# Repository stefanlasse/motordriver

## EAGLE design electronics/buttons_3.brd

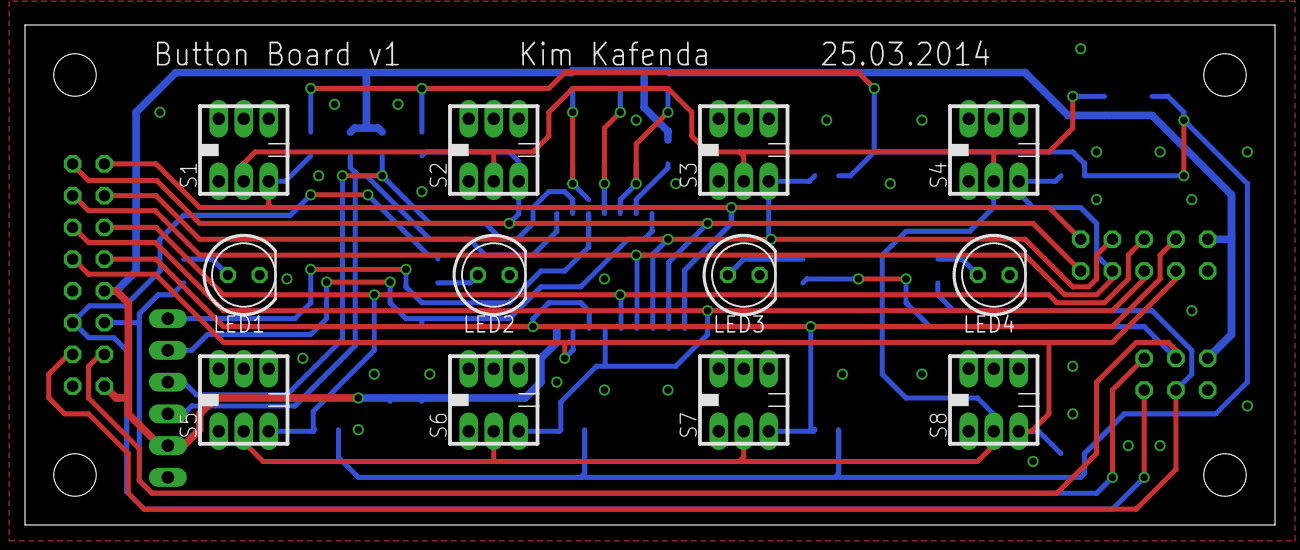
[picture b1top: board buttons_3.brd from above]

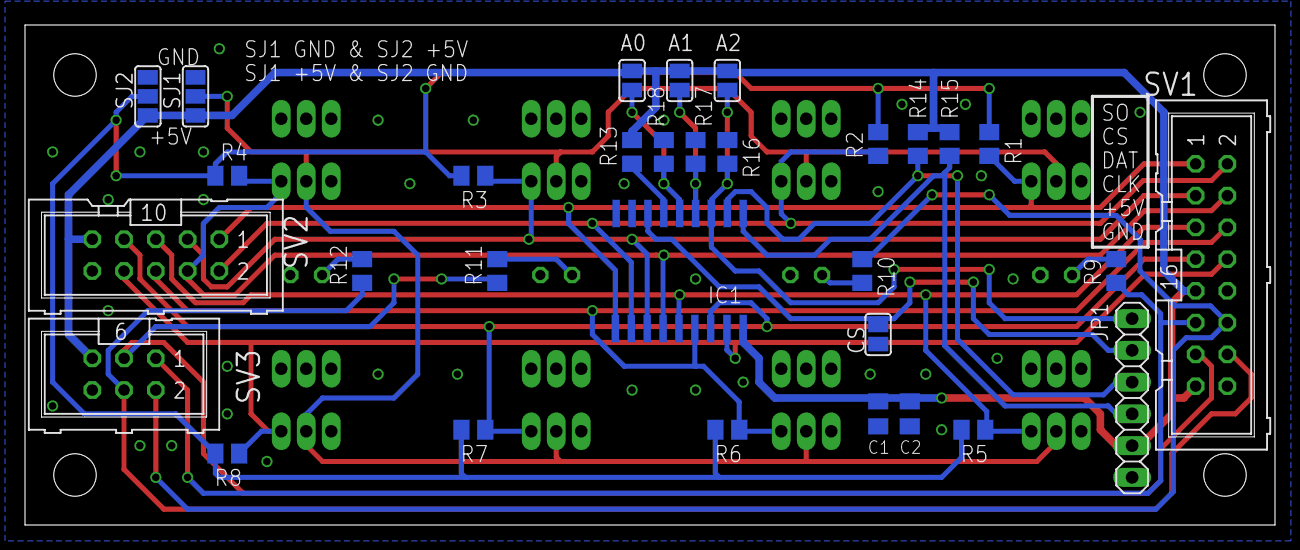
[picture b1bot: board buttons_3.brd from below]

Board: 2 copper layers, 100.0 x 40.0 mm, 43 parts (31 on the bottom side), 27 nets.

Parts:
A0, A1, A2: SJ
C1: 100nF; C0805K
C2: 10µF; C0805K
CS: SJ
IC1: MCP23008/MCP23S08/SO; SO18W
JP1: 1X06
LED1, LED2, LED3, LED4: LED5MM
R1, R2, R3, R4, R5, R6, R7, R8, R13, R16, R17, R18: 10k; M0805
R9, R10, R11, R12: 1k; M0805
R14, R15: 4k7; M0805
S1, S2, S3, S4, S5, S6, S7, S8: SWITCH_7X7
SJ1, SJ2: SJ_2
SV1: ML16
SV2: ML10
SV3: ML6

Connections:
+5V: A0.1, A1.1, A2.1, C1.1, C2.1, IC1.18, JP1.5, R13.1, R14.2, R15.2, SJ1.3, SJ2.3, SV1.9, SV1.15, SV2.9, SV3.5
CS: CS.2, IC1.7, JP1.2
GND: C1.2, C2.2, CS.1, IC1.9, JP1.6, LED1.K, LED2.K, LED3.K, LED4.K, R16.1, R17.1, R18.1, SJ1.1, SJ2.1, SV1.10, SV1.16, SV2.10, SV3.6
LED1: R9.1, SV1.11, SV3.1
LED2: R10.1, SV1.12, SV3.2
LED3: R11.1, SV1.13, SV3.3
LED4: R12.1, SV1.14, SV3.4
unnamed: LED1.A, R9.2
unnamed: IC1.6, R13.2
unnamed: LED2.A, R10.2
unnamed: LED3.A, R11.2
unnamed: LED4.A, R12.2
unnamed: A1.2, IC1.4, R17.2
unnamed: A0.2, IC1.5, R18.2
PULL: R1.2, R2.2, R3.2, R4.2, R5.2, R6.2, R7.2, R8.2, SJ2.2
S1: IC1.10, R1.1, S1.P$3, SV1.1, SV2.1
S2: IC1.11, R2.1, S2.P$3, SV1.2, SV2.2
S3: IC1.12, R3.1, S3.P$3, SV1.3, SV2.3
S4: IC1.13, R4.1, S4.P$3, SV1.4, SV2.4
S5: IC1.14, R5.1, S5.P$3, SV1.5, SV2.5
S6: IC1.15, R6.1, S6.P$3, SV1.6, SV2.6
S7: IC1.16, R7.1, S7.P$3, SV1.7, SV2.7
S8: IC1.17, R8.1, S8.P$3, SV1.8, SV2.8
SCL: IC1.1, JP1.4, R15.1
SDA: IC1.2, JP1.3, R14.1
SO: A2.2, IC1.3, JP1.1, R16.2
UP/DOWN: S1.P$2, S2.P$2, S3.P$2, S4.P$2, S5.P$2, S6.P$2, S7.P$2, S8.P$2, SJ1.2

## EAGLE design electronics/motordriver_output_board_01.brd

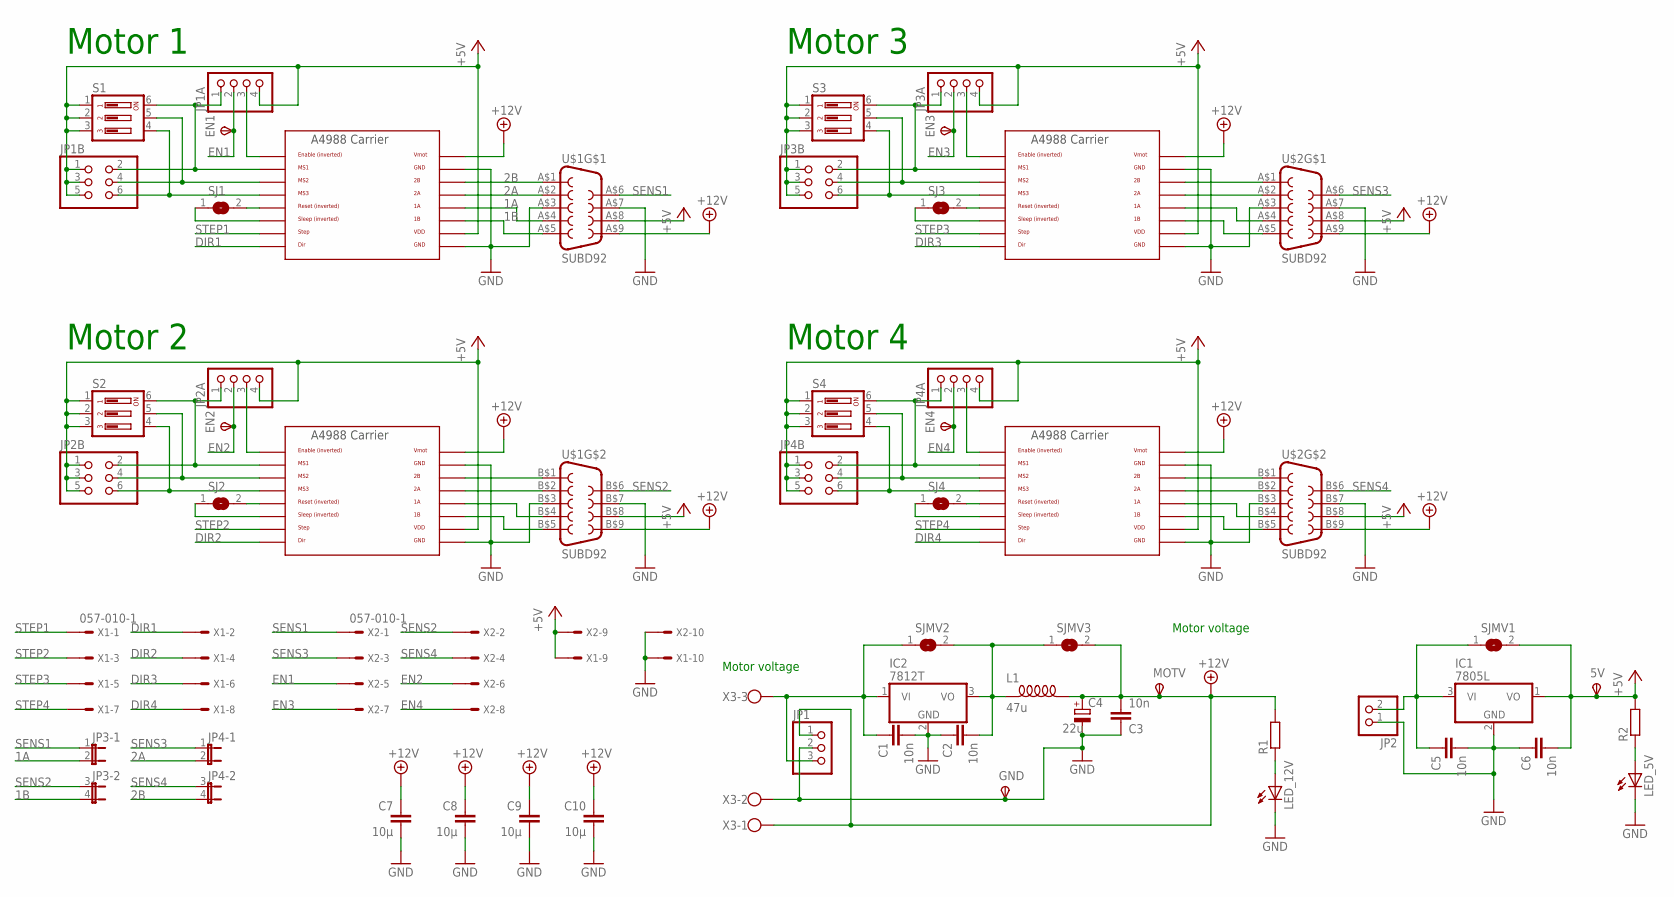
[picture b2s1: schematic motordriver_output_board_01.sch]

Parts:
5V: TPSPAD1-13; P1-13
C1, C2, C3, C5, C6: 10n; C0805
C4: 22u; 153CLV-0605
C7, C8, C9, C10: 10µ; C0805
EN1, EN2, EN3, EN4: TPSPAD1-13; P1-13
GND: TPSPAD1-13; P1-13
IC1: 7805L; TO92
IC2: 7812T; TO220H
JP1: PINHD-1X3; 1X03
JP1A, JP2A, JP3A, JP4A: PINHD-1X4; 1X04
JP1B, JP2B, JP3B, JP4B: PINHD-2X3; 2X03
JP2: PINHD-1X2; 1X02
JP3, JP4: JP2QE; JP2Q
L1: 47u; D10F
LED_5V, LED_12V: LEDCHIP-LED0805; CHIP-LED0805
MOTDRV1, MOTDRV2, MOTDRV3, MOTDRV4: A4988BREAKOUT
MOTV: TPSPAD1-13; P1-13
R1, R2: R-EU_M0805; M0805
S1, S2, S3, S4: DIP03YL
SJ1, SJ2, SJ3, SJ4: SJ
SJMV1, SJMV2, SJMV3: SJW
U$1, U$2: SUBD92; SUBD9-2
X1, X2: 057-010-1
X3: W237-103

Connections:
1A: JP3.2, MOTDRV1.1A, U$1.A$4 (4)
1A4: MOTDRV4.1A, U$2.B$4 (4)
1B: JP3.4 (2), MOTDRV1.1B, U$1.A$5 (5)
1B4: MOTDRV4.1B, U$2.B$5 (5)
2A: JP4.2, MOTDRV1.2A, U$1.A$2 (2)
2A4: MOTDRV4.2A, U$2.B$2 (2)
2B: JP4.4 (2), MOTDRV1.2B, U$1.A$1 (1)
2B4: MOTDRV4.2B, U$2.B$1 (1)
+5V: 5V.TP, C6.2, IC1.1 (VO), JP1A.4, JP1B.1, JP1B.3, JP1B.5, JP2A.4, JP2B.1, JP2B.3, JP2B.5, JP3A.4, JP3B.1, JP3B.3, JP3B.5, JP4A.4, JP4B.1, JP4B.3, JP4B.5, MOTDRV1.VDD, MOTDRV2.VDD, MOTDRV3.VDD, MOTDRV4.VDD, R2.2, S1.1, S1.2, S1.3, S2.1, S2.2, S2.3, S3.1, S3.2, S3.3, S4.1, S4.2, S4.3, SJMV1.2, U$1.A$8 (8), U$1.B$8 (8), U$2.A$8 (8), U$2.B$8 (8), X1.9, X2.9
+12V: C3.2, C4.+, C7.1, C8.1, C9.1, C10.1, JP1.1, L1.2, MOTDRV1.VMOT, MOTDRV2.VMOT, MOTDRV3.VMOT, MOTDRV4.VMOT, MOTV.TP, R1.2, SJMV3.2, U$1.A$9 (9), U$1.B$9 (9), U$2.A$9 (9), U$2.B$9 (9), X3.1
DIR1: MOTDRV1.DIR, X1.2
DIR2: MOTDRV2.DIR, X1.4
DIR3: MOTDRV3.DIR, X1.6
DIR4: MOTDRV4.DIR, X1.8
EN1: EN1.TP, JP1A.2, X2.5
EN2: EN2.TP, JP2A.2, X2.6
EN3: EN3.TP, JP3A.2, X2.7
EN4: EN4.TP, JP4A.2, X2.8
GND: C1.2, C2.1, C3.1, C4.-, C5.2, C6.1, C7.2, C8.2, C9.2, C10.2, GND.TP, IC1.2 (GND), IC2.2 (GND), JP1.2, JP2.1, LED_5V.C, LED_12V.C, MOTDRV1.GND, MOTDRV1.GND@0 (GND), MOTDRV2.GND, MOTDRV2.GND@0 (GND), MOTDRV3.GND, MOTDRV3.GND@0 (GND), MOTDRV4.GND, MOTDRV4.GND@0 (GND), U$1.A$3 (3), U$1.A$7 (7), U$1.B$3 (3), U$1.B$7 (7), U$2.A$3 (3), U$2.A$7 (7), U$2.B$3 (3), U$2.B$7 (7), X1.10, X2.10, X3.2
unnamed: MOTDRV2.2B, U$1.B$1 (1)
unnamed: LED_12V.A, R1.1
unnamed: C5.1, IC1.3 (VI), JP2.2, SJMV1.1
unnamed: MOTDRV2.2A, U$1.B$2 (2)
unnamed: LED_5V.A, R2.1
unnamed: C2.2, IC2.3 (VO), L1.1, SJMV2.2, SJMV3.1
unnamed: MOTDRV2.RST, SJ2.2
unnamed: JP2A.1, JP2B.2, MOTDRV2.MS1, S2.6
unnamed: JP2B.4, MOTDRV2.MS2, S2.5
unnamed: JP2B.6, MOTDRV2.MS3, S2.4
unnamed: MOTDRV2.1A, U$1.B$4 (4)
unnamed: MOTDRV2.1B, U$1.B$5 (5)
unnamed: MOTDRV2.SLP (SLEEP), SJ2.1
unnamed: JP2A.3, MOTDRV2.EN
unnamed: MOTDRV3.2B, U$2.A$1 (1)
unnamed: MOTDRV3.2A, U$2.A$2 (2)
unnamed: MOTDRV3.RST, SJ3.2
unnamed: JP3A.1, JP3B.2, MOTDRV3.MS1, S3.6
unnamed: JP3B.4, MOTDRV3.MS2, S3.5
unnamed: MOTDRV1.RST, SJ1.2
unnamed: MOTDRV1.SLP (SLEEP), SJ1.1
unnamed: JP3B.6, MOTDRV3.MS3, S3.4
unnamed: MOTDRV3.1A, U$2.A$4 (4)
unnamed: MOTDRV3.1B, U$2.A$5 (5)
unnamed: MOTDRV3.SLP (SLEEP), SJ3.1
unnamed: JP1A.3, MOTDRV1.EN
unnamed: JP3A.3, MOTDRV3.EN
unnamed: MOTDRV4.RST, SJ4.2
unnamed: JP4A.1, JP4B.2, MOTDRV4.MS1, S4.6
unnamed: JP4B.4, MOTDRV4.MS2, S4.5
unnamed: JP4B.6, MOTDRV4.MS3, S4.4
unnamed: MOTDRV4.SLP (SLEEP), SJ4.1
unnamed: JP4A.3, MOTDRV4.EN
unnamed: JP1A.1, JP1B.2, MOTDRV1.MS1, S1.6
unnamed: JP1B.4, MOTDRV1.MS2, S1.5
unnamed: JP1B.6, MOTDRV1.MS3, S1.4
unnamed: C1.1, IC2.1 (VI), JP1.3, SJMV2.1, X3.3
SENS1: JP3.1, U$1.A$6 (6), X2.1
SENS2: JP3.3 (1), U$1.B$6 (6), X2.2
SENS3: JP4.1, U$2.A$6 (6), X2.3
SENS4: JP4.3 (1), U$2.B$6 (6), X2.4
STEP1: MOTDRV1.STEP, X1.1
STEP2: MOTDRV2.STEP, X1.3
STEP3: MOTDRV3.STEP, X1.5
STEP4: MOTDRV4.STEP, X1.7

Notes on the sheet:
Motor voltage
Motor 1
Motor 2
Motor 3
Motor 4

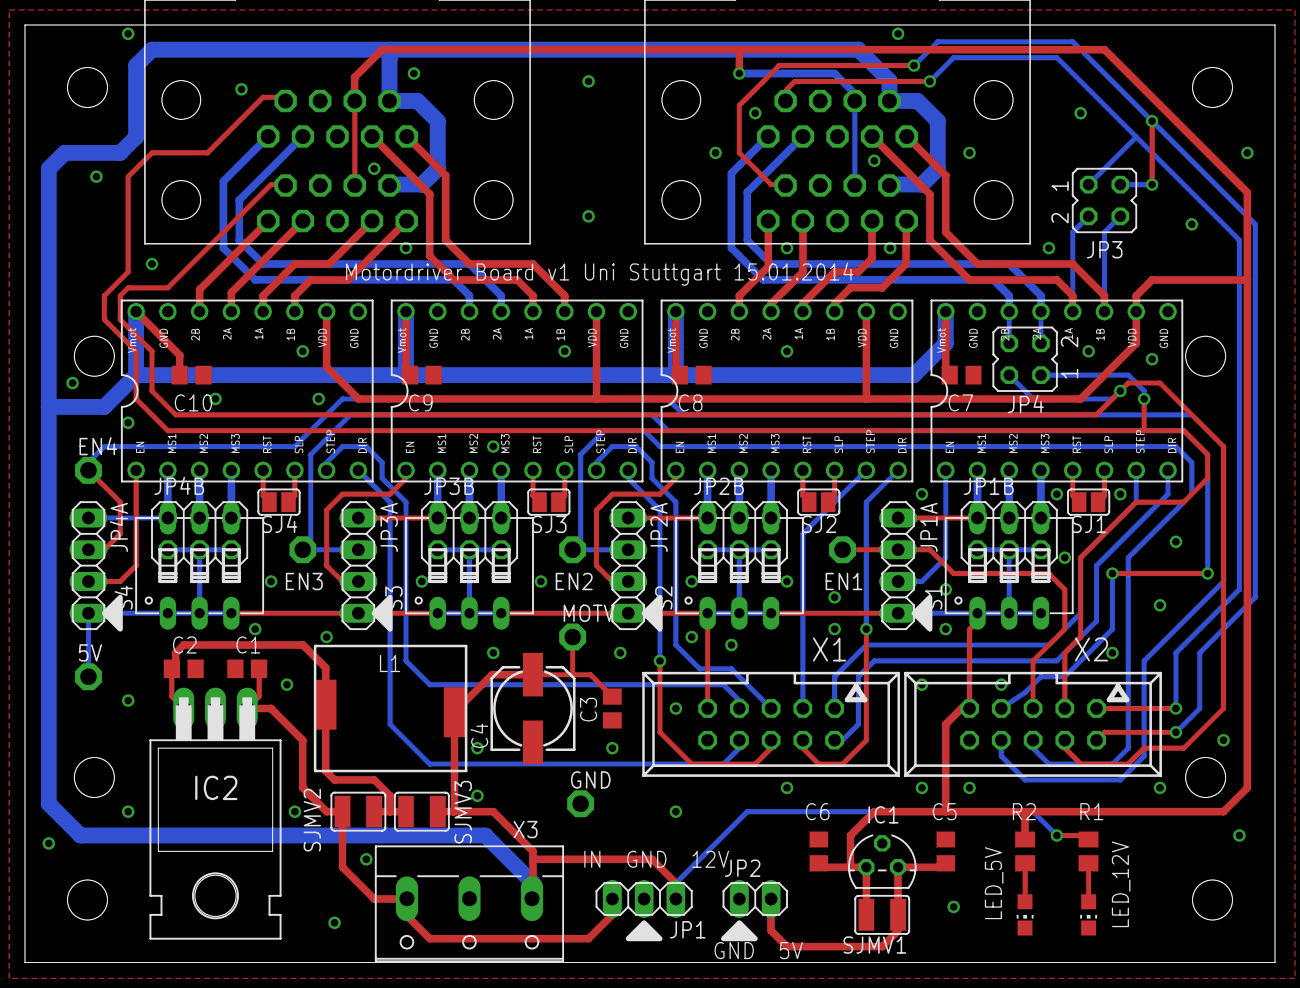
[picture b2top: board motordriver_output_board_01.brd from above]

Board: 2 copper layers, 100.0 x 75.0 mm, 56 parts (0 on the bottom side), 64 nets.

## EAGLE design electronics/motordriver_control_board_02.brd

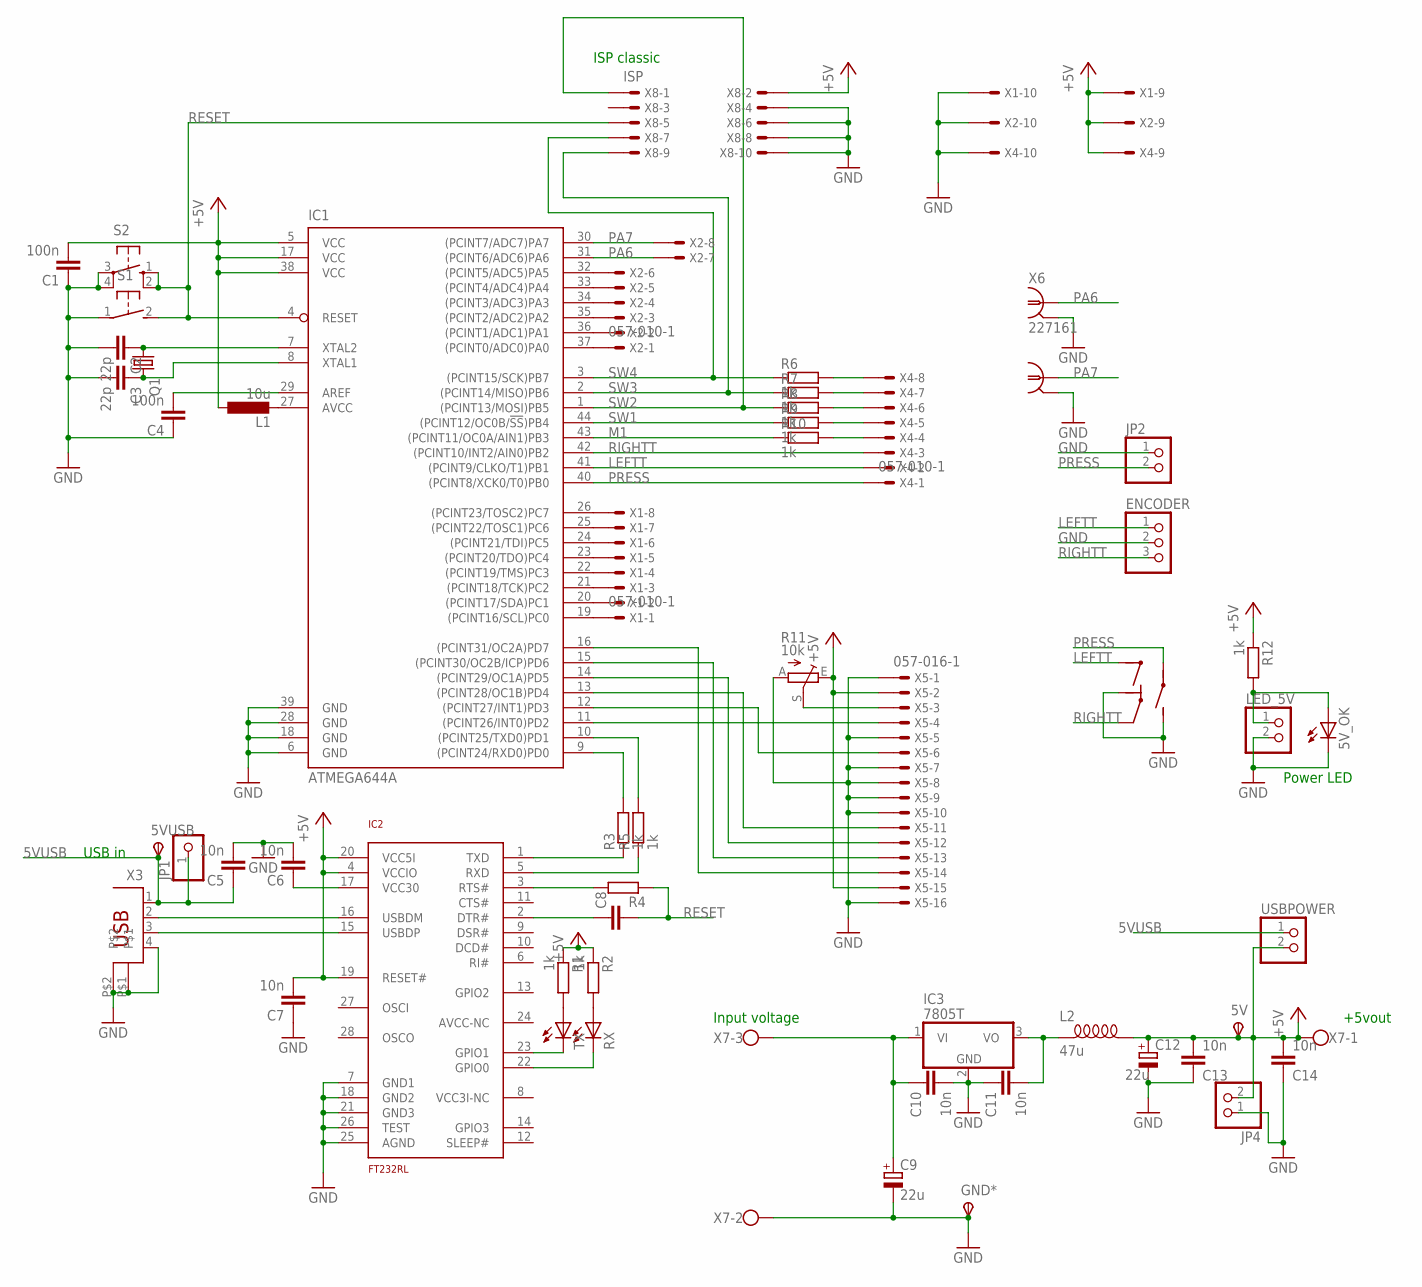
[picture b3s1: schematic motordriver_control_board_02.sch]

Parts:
5V, 5VUSB: TPSPAD1-13; P1-13
5V_OK: ZURINO_LEDCHIP-LED0805; ZURINO_CHIP-LED0805
C1, C4: 100n; C0805
C2, C3: 22p; C0805
C5, C6, C7, C10, C11, C13, C14: 10n; C0805
C8: C-EUC0805; C0805
C9, C12: 22u; 153CLV-0605
ENCODER: PINHD-1X3; 1X03
GND*: TPSPAD1-13; P1-13
IC1: ATMEGA644A; TQFP44
IC2: FT232RL; SMARTPRJ_SSOP28
IC3: 7805T; TO220H
JP1: PINHD-1X1; 1X01
JP2, JP4: PINHD-1X2; 1X02
L1: 10u; L1812
L2: 47u; D10F
LED_5V: PINHD-1X2; 1X02
Q1: ZURINO_CRYSTALHC49UP; ZURINO_HC49UP
R1, R2, R3, R5, R6, R7, R8, R9, R10, R12: 1k; M0805
R4: R-EU_M0805; M0805
R11: 10k; B64Y
RX: ZURINO_LEDCHIP-LED0805; ZURINO_CHIP-LED0805
S1: ZURINO_31-XX; ZURINO_OMRON_SW
S2: 10-XX; B3F-10XX
TX: ZURINO_LEDCHIP-LED0805; ZURINO_CHIP-LED0805
U$1: ENCODERW; DREHENC
USBPOWER: PINHD-1X2; 1X02
X1, X2, X4: 057-010-1
X3: SMARTPRJ_PN61729
X5: 057-016-1
X6: 227161; AMP_227161
X7: W237-103
X8: ISP; 057-010-1

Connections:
5VUSB: 5VUSB.TP, C5.1, JP1.1, USBPOWER.1, X3.1
+5V: 5V.TP, C1.2, C7.2, C12.+, C13.2, C14.2, IC1.5 (VCC), IC1.17 (VCC), IC1.38 (VCC), IC2.4 (VCCIO), IC2.19 (RESET#), IC2.20 (VCC5I), JP4.2, L1.1, L2.2, R1.1, R2.1, R11.E, R12.1, USBPOWER.2, X1.9, X2.9, X4.9, X5.2, X5.15, X7.1, X8.2
GND: 5V_OK.C, C1.1, C2.2, C3.2, C4.1, C5.2, C6.2, C7.1, C9.-, C10.2, C11.1, C12.-, C13.1, C14.1, ENCODER.2, GND*.TP, IC1.6 (GND), IC1.18 (GND), IC1.28 (GND), IC1.39 (GND), IC2.7 (GND1), IC2.18 (GND2), IC2.21 (GND3), IC2.25 (AGND), IC2.26 (TEST), IC3.2 (GND), JP2.1, JP4.1, LED_5V.2, R11.A, S1.1, S2.3, S2.4 (P1), U$1.P$2, U$1.P$5, X1.10, X2.10, X3.4, X3.P$1, X3.P$2, X4.10, X5.1, X5.5, X5.7, X5.8, X5.9, X5.10, X5.16, X6.1_GND, X6.2_GND, X7.2, X8.4, X8.6, X8.8, X8.10
LEFTT: ENCODER.1, IC1.41 ((PCINT9/CLKO/T1)PB1), U$1.P$1, X4.2
M1: IC1.43 ((PCINT11/OC0A/AIN1)PB3), R10.1
unnamed: IC1.19 ((PCINT16/SCL)PC0), X1.1
unnamed: IC1.9 ((PCINT24/RXD0)PD0), R3.2
unnamed: IC1.27 (AVCC), L1.2
unnamed: IC1.20 ((PCINT17/SDA)PC1), X1.2
unnamed: C2.1, IC1.7 (XTAL2), Q1.1
unnamed: C3.1, IC1.8 (XTAL1), Q1.2
unnamed: C4.2, IC1.29 (AREF)
unnamed: IC1.10 ((PCINT25/TXD0)PD1), R5.2
unnamed: IC2.1 (TXD), R3.1
unnamed: IC1.11 ((PCINT26/INT0)PD2), X5.4
unnamed: R11.S, X5.3
unnamed: IC1.12 ((PCINT27/INT1)PD3), X5.6
unnamed: IC1.21 ((PCINT18/TCK)PC2), X1.3
unnamed: IC1.22 ((PCINT19/TMS)PC3), X1.4
unnamed: IC1.23 ((PCINT20/TDO)PC4), X1.5
unnamed: C9.+, C10.1, IC3.1 (VI), X7.3
unnamed: IC1.24 ((PCINT21/TDI)PC5), X1.6
unnamed: IC2.5 (RXD), R5.1
unnamed: IC1.25 ((PCINT22/TOSC1)PC6), X1.7
unnamed: IC1.26 ((PCINT23/TOSC2)PC7), X1.8
unnamed: IC1.37 ((PCINT0/ADC0)PA0), X2.1
unnamed: IC1.36 ((PCINT1/ADC1)PA1), X2.2
unnamed: IC1.35 ((PCINT2/ADC2)PA2), X2.3
unnamed: IC1.34 ((PCINT3/ADC3)PA3), X2.4
unnamed: IC1.33 ((PCINT4/ADC4)PA4), X2.5
unnamed: IC1.32 ((PCINT5/ADC5)PA5), X2.6
unnamed: R10.2, X4.4
unnamed: R9.2, X4.5
unnamed: R8.2, X4.6
unnamed: R7.2, X4.7
unnamed: R6.2, X4.8
unnamed: IC1.14 ((PCINT29/OC1A)PD5), X5.12
unnamed: IC2.16 (USBDM), X3.2
unnamed: IC2.15 (USBDP), X3.3
unnamed: IC2.23 (GPIO1), TX.C
unnamed: IC2.22 (GPIO0), RX.C
unnamed: R2.2, RX.A
unnamed: R1.2, TX.A
unnamed: C6.1, IC2.17 (VCC30)
unnamed: C8.1, IC2.2 (DTR#)
unnamed: IC2.3 (RTS#), R4.2
unnamed: IC1.13 ((PCINT28/OC1B)PD4), X5.11
unnamed: IC1.15 ((PCINT30/OC2B/ICP)PD6), X5.13
unnamed: IC1.16 ((PCINT31/OC2A)PD7), X5.14
unnamed: 5V_OK.A, LED_5V.1, R12.2
unnamed: C11.2, IC3.3 (VO), L2.1
PA6: IC1.31 ((PCINT6/ADC6)PA6), X2.7, X6.1
PA7: IC1.30 ((PCINT7/ADC7)PA7), X2.8, X6.2
PRESS: IC1.40 ((PCINT8/XCK0/T0)PB0), JP2.2, U$1.P$4, X4.1
RESET: C8.2, IC1.4 (RESET), R4.1, S1.2 (S), S2.1 (S), S2.2 (S1), X8.5
RIGHTT: ENCODER.3, IC1.42 ((PCINT10/INT2/AIN0)PB2), U$1.P$3, X4.3
SW1: IC1.44 ((PCINT12/OC0B/!SS!)PB4), R9.1
SW2: IC1.1 ((PCINT13/MOSI)PB5), R8.1, X8.1
SW3: IC1.2 ((PCINT14/MISO)PB6), R7.1, X8.9
SW4: IC1.3 ((PCINT15/SCK)PB7), R6.1, X8.7

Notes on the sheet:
ISP classic
USB in
Power LED
+5vout
Input voltage

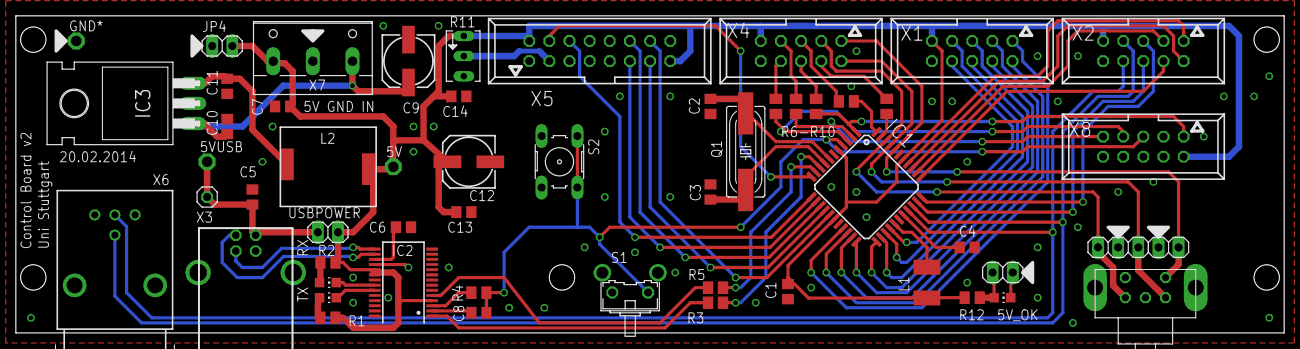
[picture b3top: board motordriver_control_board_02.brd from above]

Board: 2 copper layers, 160.0 x 40.0 mm, 55 parts (0 on the bottom side), 60 nets.

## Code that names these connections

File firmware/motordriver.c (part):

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#define DUMMY_MOTOR         4
#define MAX_MOTOR           MOTOR3  //set to MOTOR1 for 2 or MOTOR3 for 4 channel version

#define MOTOR_SENS0         PA0
#define MOTOR_SENS1         PA1
#define MOTOR_SENS2         PA2
#define MOTOR_SENS3         PA3
#define MOTOR_SENS_MAX      MOTOR_SENS3

/* define the button pinout on AVR */
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#define GREEN   1
#define BLUE    0

#define WS2803_CKI  PC7
#define WS2803_SDI  PC6

#define LED_MOT0    0
#define LED_MOT1    1
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#define CW_MOVE     1
#define CCW_MOVE   -1

#define PHASE_A  (PINC & 1<<PC5)
#define PHASE_B  (PINC & 1<<PC4)
#define DYNAMICS 40


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void initManualOperatingButtons(void){

  /* only for rotary encoder + its button */
  PORTC |= (1<<PC5)|(1<<PC4)|(1<<PC3);   /* set internal pull-ups */

  /* init port expander for buttons
   *
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  uint8_t tmp = 0;
  tmp = readPortExpanderRegister(IIC_BUTTON_PORTEXP_ADDR, GPIO);

  /* activate interrupt on INT0 (PD2) */
  EICRA |= (1<<ISC01)|(1<<ISC00);  /* rising edge causes interrupt */
  EIMSK |= (1<<INT0);   /* enable interrupt pin INT0 */

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
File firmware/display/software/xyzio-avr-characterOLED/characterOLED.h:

/*
 * characterOLED.h
 *
 * Created: 12/23/2014 4:52:46 PM
 *  Author: mkapoor
 */ 


#ifndef CHARACTEROLED_H_
#define CHARACTEROLED_H_

#define F_CPU 20000000

#include <inttypes.h>
#include <avr/pgmspace.h>
#include <avr/interrupt.h>
#include <stdio.h>
#include <string.h>
#include <stdlib.h>
#include <inttypes.h>
#include <avr/io.h>
#include <util/delay.h>

//#include "Print.h"

// OLED hardware versions
#define OLED_V1 0x01
#define OLED_V2 0x02

// commands
#define LCD_CLEARDISPLAY 0x01
#define LCD_RETURNHOME 0x02
#define LCD_ENTRYMODESET 0x04
#define LCD_DISPLAYCONTROL 0x08
#define LCD_CURSORSHIFT 0x10
#define LCD_FUNCTIONSET 0x28
#define LCD_SETCGRAMADDR 0x40
#define LCD_SETDDRAMADDR 0x80

// flags for display entry mode
#define LCD_ENTRYRIGHT 0x00
#define LCD_ENTRYLEFT 0x02
#define LCD_ENTRYSHIFTINCREMENT 0x01
#define LCD_ENTRYSHIFTDECREMENT 0x00

// flags for display on/off control
#define LCD_DISPLAYON 0x04
#define LCD_DISPLAYOFF 0x00
#define LCD_CURSORON 0x02
#define LCD_CURSOROFF 0x00
#define LCD_BLINKON 0x01
#define LCD_BLINKOFF 0x00

// flags for display/cursor shift
#define LCD_DISPLAYMOVE 0x08
#define LCD_CURSORMOVE 0x00
#define LCD_MOVERIGHT 0x04
#define LCD_MOVELEFT 0x00

// flags for function set
#define LCD_8BITMODE    0x10
#define LCD_4BITMODE    0x00
#define LCD_JAPANESE    0x00
#define LCD_EUROPEAN_I  0x01
#define LCD_RUSSIAN     0x02
#define LCD_EUROPEAN_II 0x03

// Defines for pins
	// PB3 - enable
	// PB2 - rw (read / write)
	// PB1 - rs (reg select)
	// PB7 - Data 7 / busy
	// PB6 - Data 6
	// PB5 - Data 5
	// PB4 - Data 4

#define _enable_pin	3
#define _rw_pin		2
#define rs_pin		1
#define data4		4
#define data5		5
#define data6		6
#define _busy_pin	7
#define data7		7

#define OUTPUT		1
#define INPUT		0

// define Port
#define LCD_PORT PORTB
#define LCD_DDR DDRB
#define LCD_PIN PINB

#define LOW			0
#define HIGH		1



class characterOLED {
	public:
	characterOLED(uint8_t ver);
	
	void init(uint8_t ver);
	
	void begin(uint8_t cols, uint8_t rows);

	void clear();
	void home();

	void noDisplay();
	void display();
	void noBlink();
	void blink();
	void noCursor();
	void cursor();
	void scrollDisplayLeft();
	void scrollDisplayRight();
	void leftToRight();
	void rightToLeft();
	void autoscroll();
	void noAutoscroll();
	void digitalWrite(uint8_t pin,uint8_t value);
	uint8_t digitalRead(uint8_t pin);

	void createChar(uint8_t, uint8_t[]);
	void setCursor(uint8_t, uint8_t);
	virtual size_t write(uint8_t);
	void command(uint8_t);
	
	size_t print(const char[]);
	size_t print(char);
	size_t write(const uint8_t *buffer, size_t size);
	size_t write(const char *str);
	
	private:
	void send(uint8_t, uint8_t);
	void write4bits(uint8_t);
	void pulseEnable();
	void waitForReady();
	void pinMode(uint8_t pin, uint8_t mode);
	


	uint8_t _oled_ver; // OLED_V1 = older, OLED_V2 = newer hardware version.
	//uint8_t rs_pin; // LOW: command.  HIGH: character.
	//uint8_t _rw_pin; // LOW: write to LCD.  HIGH: read from LCD.
	//uint8_t _enable_pin; // activated by a HIGH pulse.
	//uint8_t _busy_pin;   // HIGH means not ready for next command
	uint8_t _data_pins[4];

	uint8_t _displayfunction;
	uint8_t _displaycontrol;
	uint8_t _displaymode;
	uint8_t _initialized;
	uint8_t _currline;
	uint8_t _numlines;
};



#endif /* CHARACTEROLED_H_ */

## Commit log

2014-05-10 first upload
2014-05-10 motor movement outsourced in timer interrupt
2014-05-10 added ISMOVING? command
2014-05-11 outsourced command actions into extra functions
2014-05-11 added some security for command parameter
2014-05-13 added TODO list
2014-05-15 several improvements for usability
2014-05-15 bugfix in zerorun
2014-05-15 added constant angular velocity mode
2014-05-15 added memory usage script
2014-05-15 implemented optical zero position
2014-05-16 updated TODO list
2014-05-16 added facotry reset
2014-05-16 motor numbering consistency
2014-05-16 corrected more motor numbering inconsistency
2014-05-16 fixed awful motor numbering bug
2014-05-16 kim demo
2014-05-17 fixed position update bug
2014-05-17 bug fix in motor zero run
2014-05-17 implemented step error correction
2014-05-17 deleted step error printout
2014-05-17 some code cosmetics
2014-05-17 branch test
2014-05-19 added visible motor selection
2014-05-19 Version 0.3
2014-05-20 added hex-file to repository
2014-05-20 fixed motor selection toggle bug
2014-05-20 fixed menu jump bug
2014-05-20 added const angular velocity to menu
2014-05-20 bugfix in const angular velocity
2014-05-21 fixed bug in MOVEABS command
2014-05-22 implemented fast mode for motor moving
2014-05-22 implemented STOPALL command
2014-05-22 deleted gear ratio menu
2014-05-22 fixed bug: motor selection in other menu
2014-05-22 code cosmetics, fixed some warnings
2014-05-22 fixed unit bug in opt zero pos
2014-05-23 uplaod mechanics, electronics
2014-05-29 implemented a python interface
2014-05-29 wrote a useful sample program
2014-05-29 little bugfix in python-module
2014-05-30 removed some tests
2014-06-26 bug fix in menu handling
2014-06-27 bug fix in command parser
2014-06-30 update of user manual
2014-07-02 LabView interface added
2014-07-03 bug fix: constAngularSpeed
2014-07-03 bug fix: commandSetConstSpeed
2014-07-03 bug fix: commandMoveRel
2014-07-03 bug fix: commandSetGearRatio
2014-07-03 update LabView interface
2014-07-04 added factory test
2014-07-04 bug fixes in python interface
2014-07-04 manual update
2014-07-04 fixed bug: hang up after *RST
2014-07-04 update in python interface
2014-07-04 update operating manual
2014-07-04 bug fix: only powers of 2 in substeps
2014-07-04 identify fast moving mode on display
2014-07-04 removed debugging information
2014-07-04 updated operating manual
2014-07-05 update manual
2014-07-10 added software info to manual
2014-07-10 added command description to manual
2014-07-10 bug fix in const angular velocity
2014-07-10 added forbidden zones for motors
2014-07-10 added forbidden zone to manual
2014-07-10 indicate forbidden zone on display
2014-07-10 added command for turning forbidden zone on/off
2014-08-08 implemented internal programs
2014-08-08 version 1.3
2014-08-21 updated python interface
2014-08-31 bug fix in motor movement timer
2014-09-05 bug fix: save/load config display fault
2014-09-05 finalized sample python program
2014-09-05 implemented saving internal programs in EEPROM
2014-09-05 updated python-interface
2014-09-08 bug fix: bouncing of rotary encoder
2014-09-20 update to new motors gear ratio
2014-09-20 added basic i2c-functions
2014-10-11 update TODO list
2014-10-11 pufh for checkout
2014-10-11 added IIC DAC functionality
2015-05-12 fixed compiler bug, added new IIC functionality
2015-05-12 supplementary files
2015-05-12 added more DRV8825 functions
2015-05-14 fixed: port expander, rotEnc
2015-05-17 implemented OLED library
2015-05-17 code cosmetics for OLED routines
2016-01-20 implemented button port expander
2016-01-20 bugfix buttons and rotEnc
2016-01-20 implemented LEDs
2016-01-21 implemented subSteps
2016-01-21 implemented motor current
2016-01-22 fixed zero run
2016-01-27 update menu
2016-01-29 code cosmetics
2016-02-16 fix in button init routine
2016-02-16 update: compiled hex-file
2016-02-16 init PI3 branch
2016-02-16 allow more movement steps
2016-02-18 bugfix: multiple runs; implemented ZERORUNDONE command
2016-02-18 rewrite: gear ratio; now in teeth of gears
2016-02-18 bug fix: optical zero position
2016-02-18 v1.5-rc1
2016-02-19 added firmware update script
2016-02-22 update motor button LEDs
2016-02-23 implemented settings submenu
2016-02-27 implemented motor decay, bugfix in loadConfig
2016-03-26 bugfix software reset
2016-03-28 bugfix forbidden zone
2016-04-01 implemented motor detection command
2016-04-13 version 1.5.1
2016-04-20 added libiic
2016-04-20 implemented menus for gear ratio, full rotation, decay
2016-04-20 gitignore
2016-04-20 added command for display brightness
2016-04-21 implemented adjustable LED color
2016-04-21 added enable menu
2016-04-27 moved enable menu to main menu
2016-04-27 added additional LED mode
2016-05-02 update python interface
2016-05-20 implemented shorter wait times

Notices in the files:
firmware/motordriver.c:
Copyright (C) 2016 LK-Instruments
